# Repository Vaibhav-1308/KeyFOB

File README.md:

# KeyFOB
 This is the fun project made with STM32WB55 a BLE Microcontroller.
 <br>
 Author - Vaibhav Nrupnarayan.

 ### Description 
Designed and developed a Programmable Key FOB using an STM32 microcontroller, integrating Bluetooth Low Energy (BLE) technology, RGB LED, and buzzer functionality. Utilized KiCad for PCB layout and circuit design, showcasing skills in electronic prototyping and embedded systems development.
### PCB Board with STM32WB55CEU6

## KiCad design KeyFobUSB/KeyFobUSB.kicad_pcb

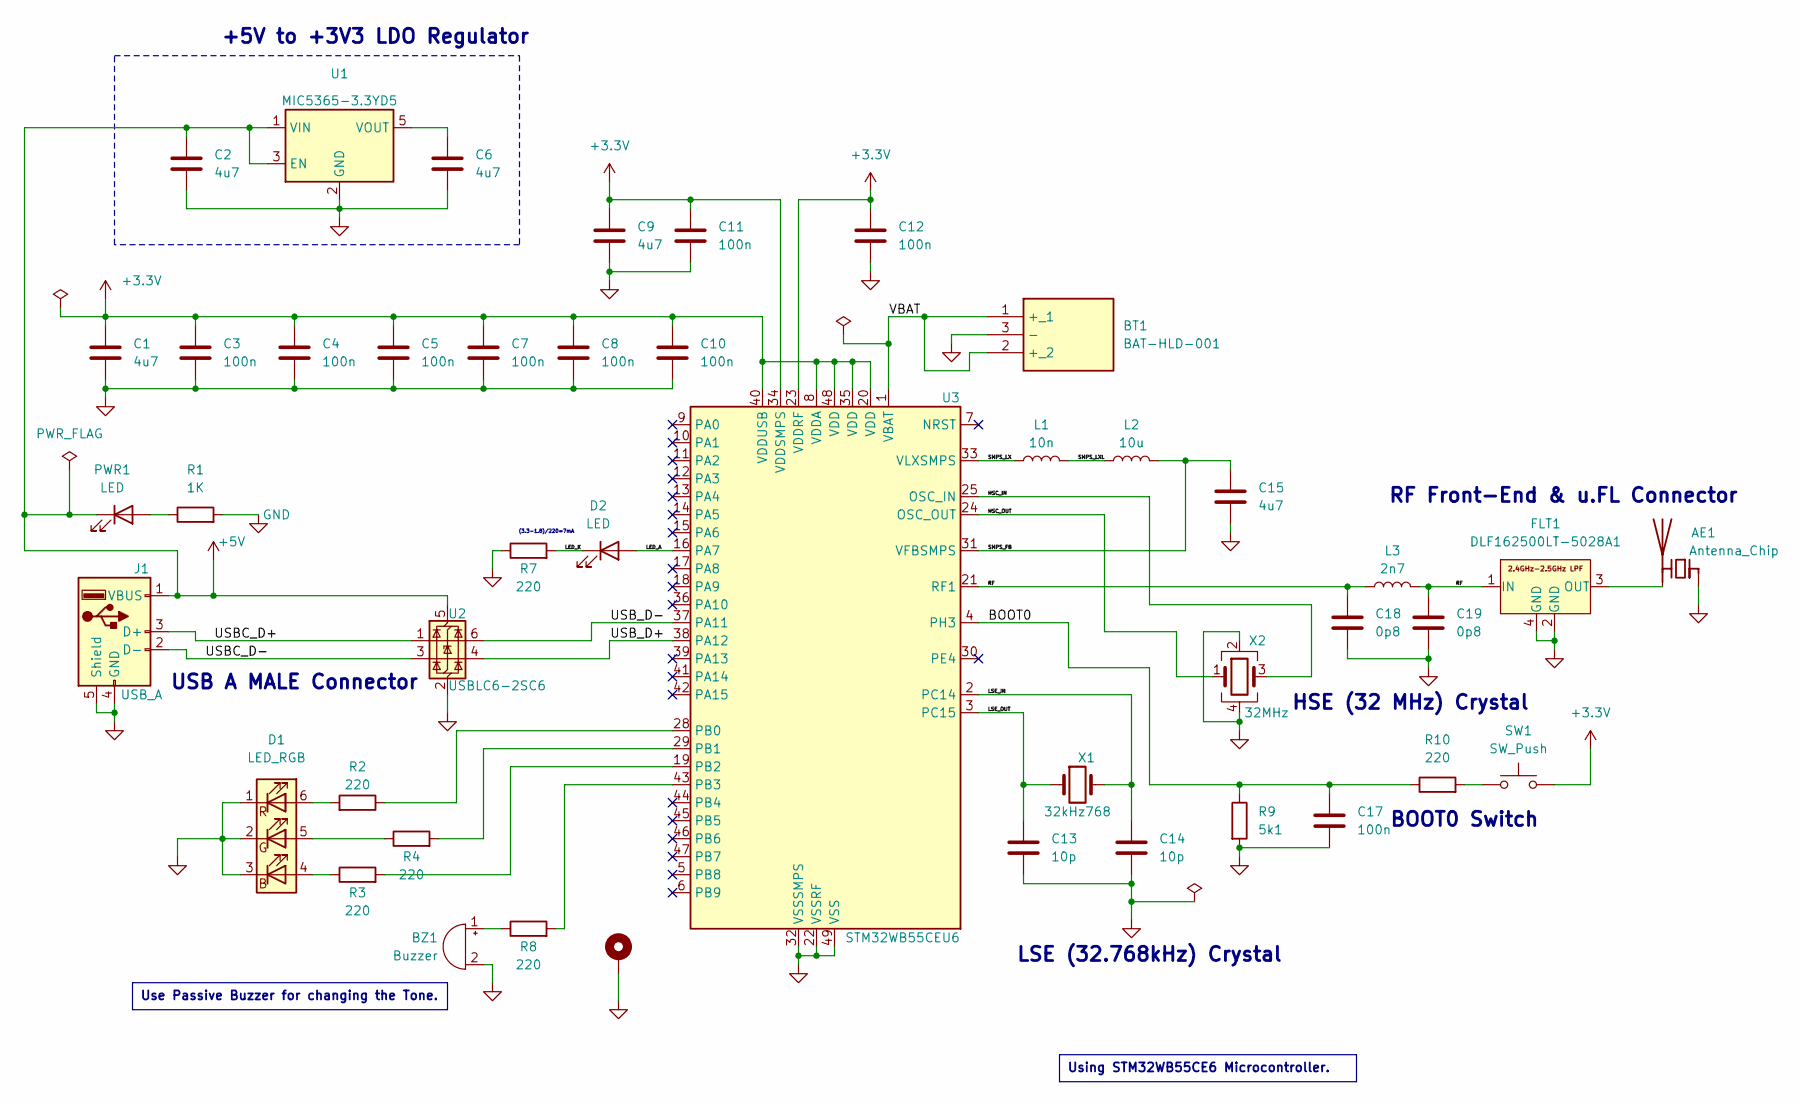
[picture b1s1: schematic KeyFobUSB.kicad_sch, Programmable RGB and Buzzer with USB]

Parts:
AE1: Antenna_Chip; RF Ceramic Antenna QJ-13799-2-2019
BT1: BAT-HLD-001; BATHLD001 CR2032; Mouser Part Number 712-BAT-HLD-001
BZ1: Buzzer; Buzzer_CUI_CPT-9019S-SMT
C1, C2, C6, C9, C15: 4u7; C_0805_2012Metric
C3, C4, C5, C7, C8, C10, C11, C12, C17: 100n; C_0805_2012Metric
C13, C14: 10p; C_0805_2012Metric
C18, C19: 0p8; C_0805_2012Metric
D1: LED_RGB; LED_Inolux_IN-P55TATRGB_PLCC6_5.0x5.5mm_P1.8mm
D2: LED; LED_0805_2012Metric
FLT1: DLF162500LT-5028A1
H+1: MountingHole_Pad; MountingHole_3mm_Pad_Via
J1: USB_A; USBonPCB
L1: 10n; L_0805_2012Metric
L2: 10u; L_0805_2012Metric
L3: 2n7; L_0805_2012Metric
PWR1: LED; LED_0805_2012Metric
R1: 1K; R_0805_2012Metric
R2, R3, R4, R7, R8, R10: 220; R_0805_2012Metric
R9: 5k1; R_0805_2012Metric
SW1: SW_Push; SW_SPST_CK_RS282G05A3
U1: MIC5365-3.3YD5; SOT-23-5
U2: USBLC6-2SC6; SOT-23-6
U3: STM32WB55CEU6; QFN-48-1EP_7x7mm_P0.5mm_EP5.6x5.6mm
X1: 32kHz768; Crystal_SMD_2012-2Pin_2.0x1.2mm
X2: 32MHz; Crystal_SMD_2016-4Pin_2.0x1.6mm

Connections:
+3.3V: C1.1, C3.1, C4.1, C5.1, C7.1, C8.1, C9.1, C10.1, C11.1, C12.1, SW1.2, U3.8 (VDDA), U3.20 (VDD), U3.23 (VDDRF), U3.34 (VDDSMPS), U3.35 (VDD), U3.40 (VDDUSB), U3.48 (VDD)
+5V: C2.1, J1.1 (VBUS), PWR1.1 (K), U1.1 (VIN), U1.3 (EN), U2.5 (VBUS)
/BOOT0: C17.1, R9.1, R10.1, U3.4 (PH3)
/HSC_IN: U3.25 (OSC_IN), X2.3
/HSC_OUT: U3.24 (OSC_OUT), X2.1
/LED_A: D2.2 (A), U3.16 (PA7)
/LED_K: D2.1 (K), R7.2
/LSE_IN: C14.1, U3.2 (PC14), X1.2
/LSE_OUT: C13.1, U3.3 (PC15), X1.1
/RF: C18.1, C19.1, FLT1.1 (IN), L3.1, L3.2, U3.21 (RF1)
/SMPS_FB: C15.1, L2.2, U3.31 (VFBSMPS)
/SMPS_LX: L1.1, U3.33 (VLXSMPS)
/SMPS_LXL: L1.2, L2.1
/USBC_D+: J1.3 (D+), U2.1 (I/O1)
/USBC_D-: J1.2 (D-), U2.3 (I/O2)
/USB_D+: U2.4 (I/O2), U3.38 (PA12)
/USB_D-: U2.6 (I/O1), U3.37 (PA11)
/VBAT: BT1.1 (+_1), BT1.2 (+_2), U3.1 (VBAT)
GND: AE1.1 (FEED), BT1.3 (-), BZ1.2 (-), C1.2, C2.2, C3.2, C4.2, C5.2, C6.2, C7.2, C8.2, C9.2, C10.2, C11.2, C12.2, C13.2, C14.2, C15.2, C17.2, C18.2, C19.2, D1.1 (RK), D1.2 (GK), D1.3 (BK), FLT1.2 (GND), FLT1.4 (GND), H+1.1, J1.4 (GND), J1.5 (Shield), R1.2, R7.1, R9.2, U1.2 (GND), U2.2 (GND), U3.22 (VSSRF), U3.32 (VSSSMPS), U3.49 (VSS), X2.2, X2.4
unnamed: AE1.2 (PCB_Trace), FLT1.3 (OUT)
unnamed: BZ1.1 (+), R8.1
unnamed: D1.4 (BA), R3.1
unnamed: D1.5 (GA), R4.1
unnamed: D1.6 (RA), R2.2
unnamed: PWR1.2 (A), R1.1
unnamed: R10.2, SW1.1
unnamed: C6.1, U1.5 (VOUT)
unnamed: R2.1, U3.28 (PB0)
unnamed: R4.2, U3.29 (PB1)
unnamed: R3.2, U3.19 (PB2)
unnamed: R8.2, U3.43 (PB3)

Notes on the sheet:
Using STM32WB55CE6 Microcontroller.
Use Passive Buzzer for changing the Tone.
LSE (32.768kHz) Crystal
(3.3-1.8)/220=7mA
USB A MALE Connector
BOOT0 Switch
RF Front-End & u.FL Connector
HSE (32 MHz) Crystal
+5V to +3V3 LDO Regulator

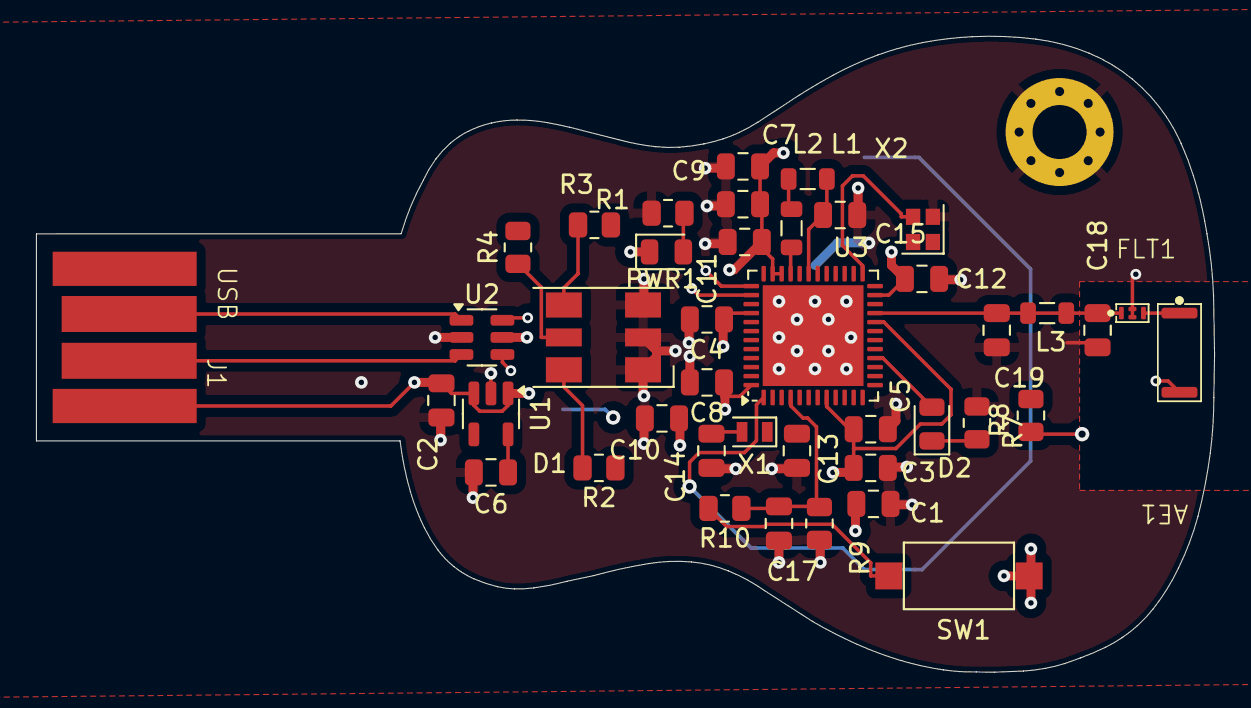
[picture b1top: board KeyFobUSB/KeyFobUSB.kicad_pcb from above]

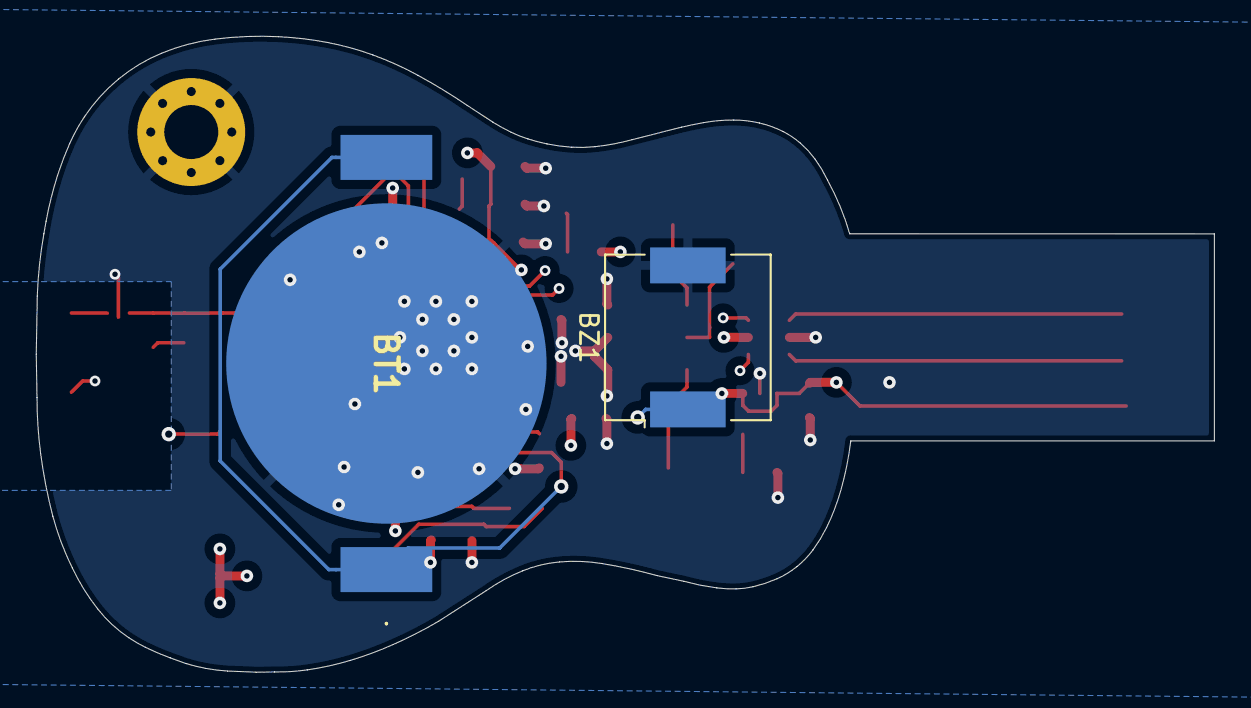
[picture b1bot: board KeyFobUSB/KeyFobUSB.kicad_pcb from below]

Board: 4 copper layers, 65.4 x 35.3 mm, 44 parts (2 on the bottom side), 31 nets.

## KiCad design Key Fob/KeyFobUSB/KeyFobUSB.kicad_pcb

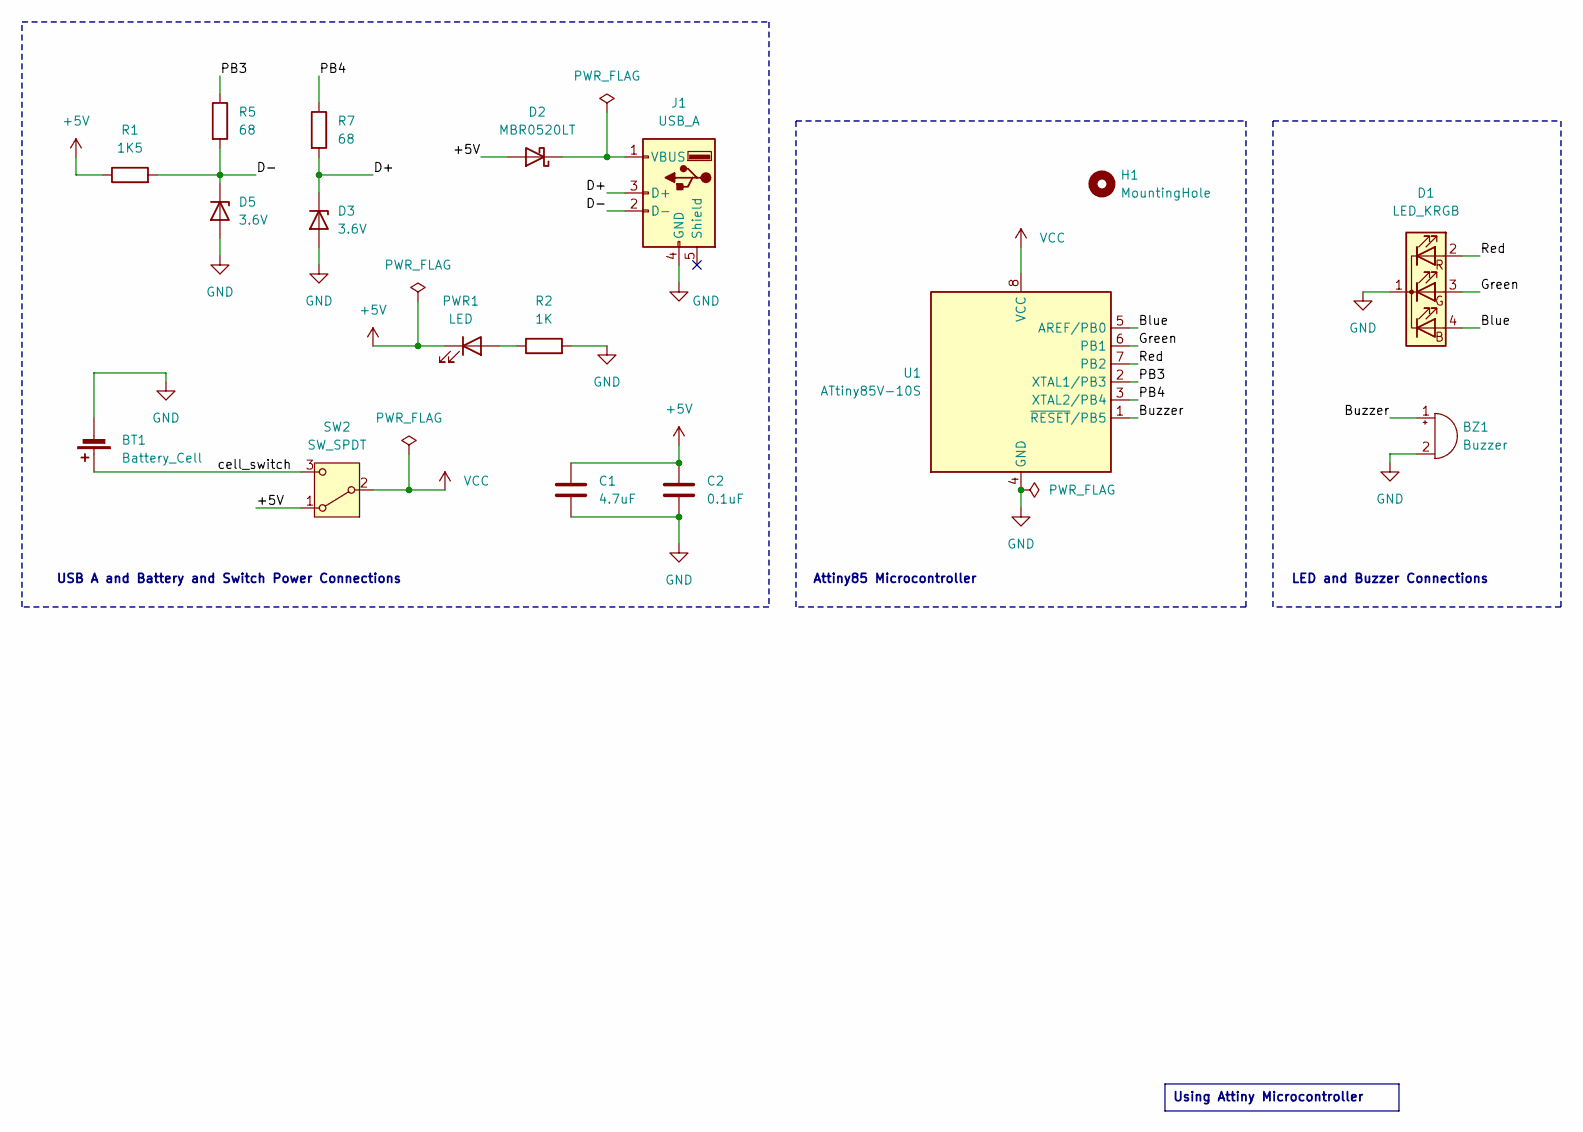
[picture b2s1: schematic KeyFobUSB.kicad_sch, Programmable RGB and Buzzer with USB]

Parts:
BT1: Battery_Cell; S8411-45R_1
BZ1: Buzzer; MagneticBuzzer_ProSignal_ABT-410-RC
C1: 4.7uF; C_0805_2012Metric
C2: 0.1uF; C_0805_2012Metric
D1: LED_KRGB; LED_D5.0mm-4_RGB
D2: MBR0520LT; D_SOD-123
D3, D5: 3.6V; D_1206_3216Metric
H1: MountingHole; MountingHole_4.3mm_M4
J1: USB_A; USBonPCB
PWR1: LED; LED_0805_2012Metric
R1: 1K5; R_0805_2012Metric
R2: 1K; R_0805_2012Metric
R5, R7: 68; R_0805_2012Metric
SW2: SW_SPDT; SW_SPDT_PCM12
U1: ATtiny85V-10S; SOIC-8W_5.3x5.3mm_P1.27mm

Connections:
+5V: C1.1, C2.1, D2.2 (A), PWR1.1 (K), R1.1, SW2.1 (A)
/Blue: D1.4 (BA), U1.5 (AREF/PB0)
/Buzzer: BZ1.1 (+), U1.1 (~RESET/PB5)
/D+: D3.1 (K), J1.3 (D+), R7.2
/D-: D5.1 (K), J1.2 (D-), R1.2, R5.2
/Green: D1.3 (GA), U1.6 (PB1)
/PB3: R5.1, U1.2 (XTAL1/PB3)
/PB4: R7.1, U1.3 (XTAL2/PB4)
/Red: D1.2 (RA), U1.7 (PB2)
/cell_switch: BT1.1 (+), SW2.3 (C)
GND: BT1.2 (-), BZ1.2 (-), C1.2, C2.2, D1.1 (K), D3.2 (A), D5.2 (A), J1.4 (GND), R2.2, U1.4 (GND)
unnamed: D2.1 (K), J1.1 (VBUS)
unnamed: PWR1.2 (A), R2.1
VCC: SW2.2 (B), U1.8 (VCC)

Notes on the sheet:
Using Attiny Microcontroller
Attiny85 Microcontroller
USB A and Battery and Switch Power Connections
LED and Buzzer Connections

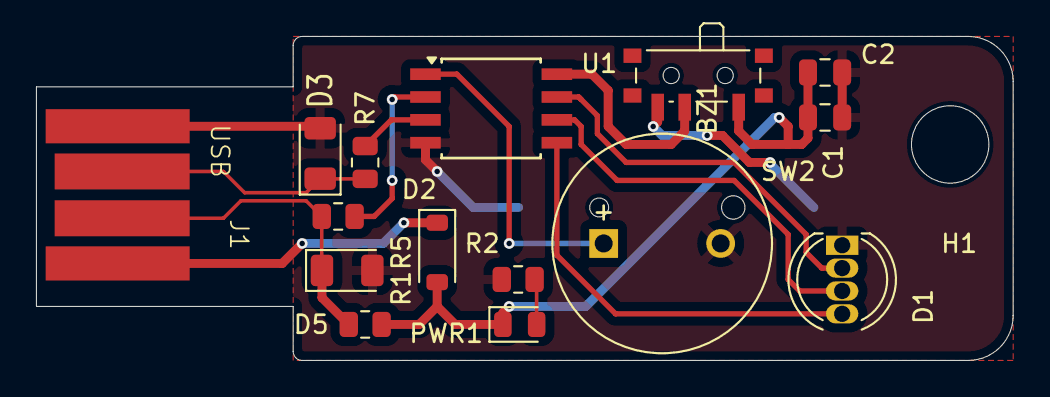
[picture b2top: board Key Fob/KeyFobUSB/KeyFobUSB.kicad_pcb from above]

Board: 2 copper layers, 54.3 x 18.0 mm, 17 parts (1 on the bottom side), 14 nets.

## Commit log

2024-07-22 Updating author name.
2024-07-22 adding project files in the folder
2024-07-22 improvement
2024-07-30 changed the backup files
2024-08-18 Changed the location due to some issues
2024-09-04 Changed the Microcontroller due to changed requirements
2024-09-19 Completed the schematic and placed the components on pcb
2024-09-21 added battery holder and vias
2024-09-23 Added the PCB image
2024-09-23 Update README.md
    Added the image of Board.
2024-09-26 Added the Docs
2024-10-08 Added the Bluetooth SMD Antenna and marked the area.
2024-11-02 Added the ceramic antenna datasheet
2024-11-27 Added the new SS
2024-11-27 Update README.md
    Added new SS.
2024-11-27 Added SS
